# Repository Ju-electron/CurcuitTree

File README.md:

# CurcuitTree
X-MAS Tree what only contain basic IC

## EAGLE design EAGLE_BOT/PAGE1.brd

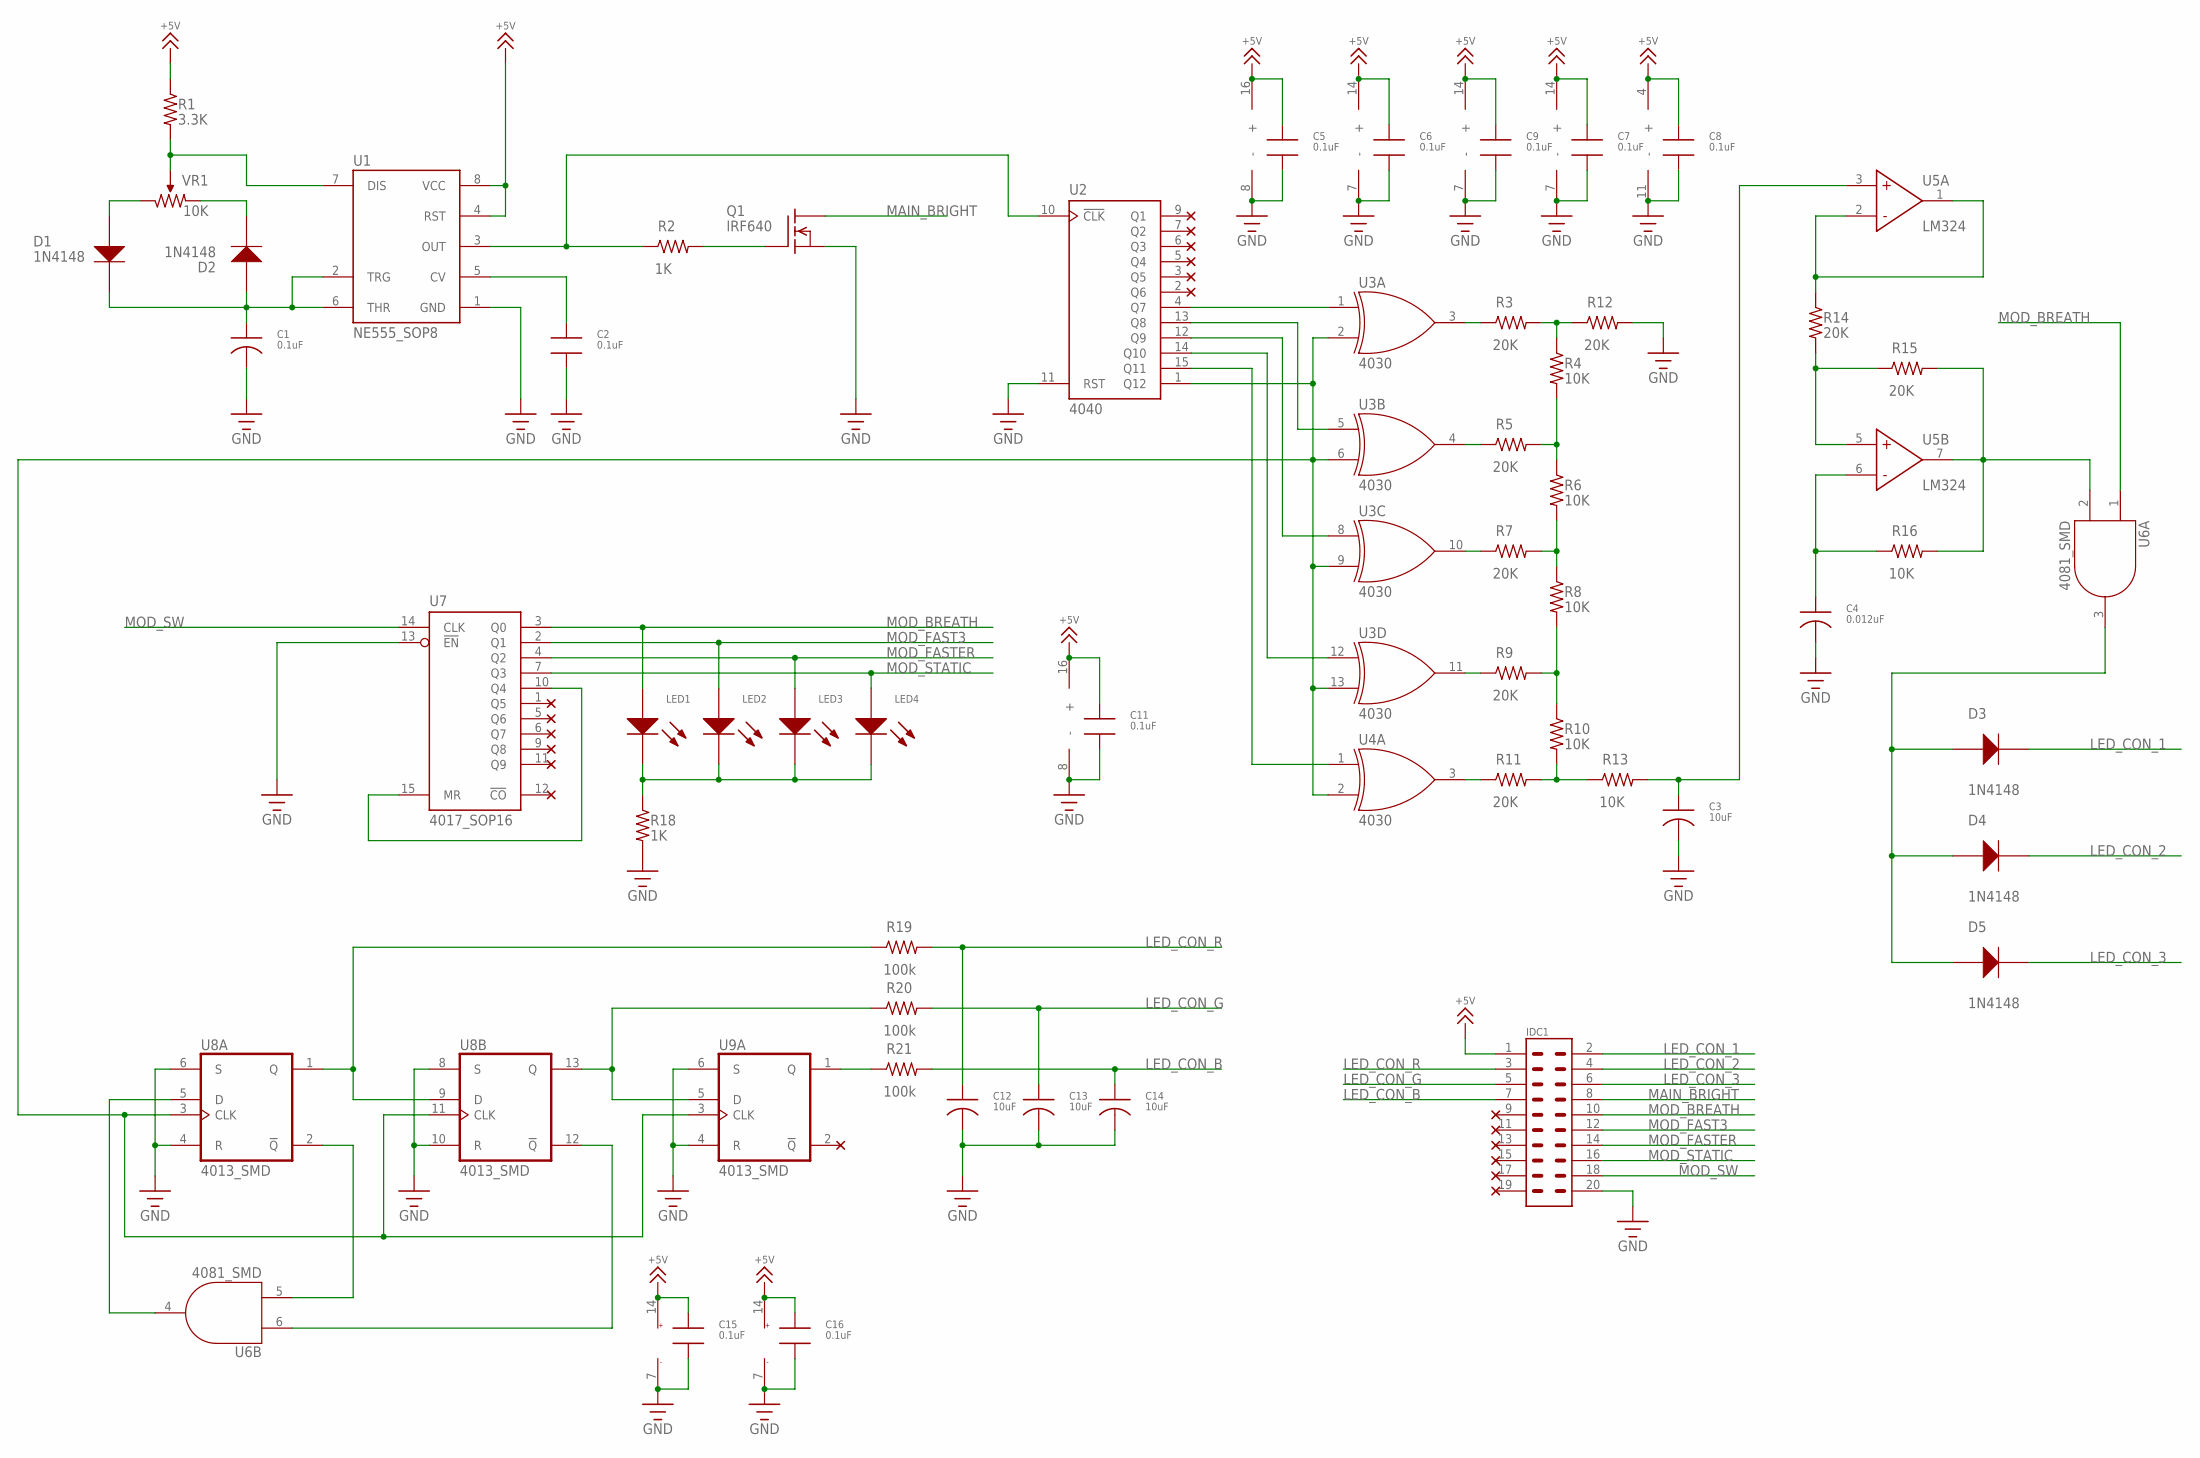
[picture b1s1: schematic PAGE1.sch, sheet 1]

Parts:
C1: 0.1uF; CAP_POL
C2, C5, C6, C7, C8, C9, C11, C15, C16: 0.1uF; SMD2012
C3, C12, C13, C14: 10uF; CAP_POL
C4: 0.012uF; CAP_POL
D1, D2, D3, D4, D5: 1N4148; SMD_DIODE
IDC1: IDC20_BEN; IDC20_BENDING
LED1, LED2, LED3, LED4: LED_BEN; LED_5MM_BEN
Q1: IRF640; TO220
R1: 3.3K; SMD2012
R2, R18: 1K; SMD2012
R3, R5, R7, R9, R11, R12, R14, R15: 20K; SMD2012
R4, R6, R8, R10, R13, R16: 10K; SMD2012
R19, R20, R21: 100k; SMD2012
U1: NE555_SOP8; SOP8
U2: 4040; DIP16
U3, U4: 4030; DIP14
U5: LM324; DIP14
U6: 4081_SMD; SOP14
U7: 4017_SOP16; SOP16
U8, U9: 4013_SMD; SOIC_14
VR1: 10K; 3RP/1610N

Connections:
+5V: C5.1, C6.1, C7.1, C8.1, C9.1, C11.1, C15.1, C16.1, IDC1.1, R1.1, U1.4 (RST), U1.8 (VCC), U2.16 (+), U3.14 (+), U4.14 (+), U5.4 (+), U6.14 (+), U7.16 (+), U8.14 (VCC), U9.14 (VCC); also elsewhere on the board
GND: C1.2, C2.2, C3.2, C4.2, C5.2, C6.2, C7.2, C8.2, C9.2, C11.2, C12.2, C13.2, C14.2, C15.2, C16.2, IDC1.20, Q1.3 (S), R12.2, R18.2, U1.1 (GND), U2.8 (-), U2.11 (RST), U3.7 (-), U4.7 (-), U5.11 (-), U6.7 (-), U7.8 (-), U7.13 (!EN), U8.4 (R), U8.6 (S), U8.7 (GND), U8.8 (S), U8.10 (R), U9.4 (R), U9.6 (S), U9.7 (GND); also elsewhere on the board
LED_CON_1: D3.2, IDC1.2; also elsewhere on the board
LED_CON_2: D4.2, IDC1.4; also elsewhere on the board
LED_CON_3: D5.2, IDC1.6; also elsewhere on the board
LED_CON_B: C14.1, IDC1.7, R21.2
LED_CON_G: C13.1, IDC1.5, R20.2
LED_CON_R: C12.1, IDC1.3, R19.2
MAIN_BRIGHT: IDC1.8, Q1.2 (D)
MOD_BREATH: IDC1.10, LED1.1, U6.1, U7.3 (Q0)
MOD_FAST3: IDC1.12, LED2.1, U7.2 (Q1); also elsewhere on the board
MOD_FASTER: IDC1.14, LED3.1, U7.4 (Q2); also elsewhere on the board
MOD_STATIC: IDC1.16, LED4.1, U7.7 (Q3); also elsewhere on the board
MOD_SW: IDC1.18, U7.14 (CLK)
unnamed: D1.1, VR1.1
unnamed: R1.2, U1.7 (DIS), VR1.2
unnamed: D2.2, VR1.3
unnamed: C2.1, U1.5 (CV)
unnamed: C1.1, D1.2, D2.1, U1.2 (TRG), U1.6 (THR)
unnamed: R2.1, U1.3 (OUT), U2.10 (!CLK)
unnamed: Q1.1 (G), R2.2
unnamed: U2.4 (Q7), U3.1 (IN1)
unnamed: U2.13 (Q8), U3.5 (IN1)
unnamed: U2.12 (Q9), U3.8 (IN1)
unnamed: U2.14 (Q10), U3.12 (IN1)
unnamed: U2.15 (Q11), U4.1 (IN1)
unnamed: R3.1, U3.3 (OUT)
unnamed: R5.1, U3.4 (OUT)
unnamed: R7.1, U3.10 (OUT)
unnamed: R9.1, U3.11 (OUT)
unnamed: R11.1, U4.3 (OUT)
unnamed: R3.2, R4.1, R12.1
unnamed: R4.2, R5.2, R6.1
unnamed: R6.2, R7.2, R8.1
unnamed: R8.2, R9.2, R10.1
unnamed: R10.2, R11.2, R13.1
unnamed: C3.1, R13.2, U5.3 (+)
unnamed: R14.1, U5.1 (OUT), U5.2 (-)
unnamed: R15.2, R16.2, U5.7 (OUT), U6.2
unnamed: R14.2, R15.1, U5.5 (+)
unnamed: C4.1, R16.1, U5.6 (-)
unnamed: D3.1, D4.1, D5.1, U6.3
unnamed: U7.10 (Q4), U7.15 (MR)
unnamed: LED1.2, LED2.2, LED3.2, LED4.2, R18.1
unnamed: U6.5, U8.2 (!Q)
unnamed: U6.6, U8.12 (!Q)
unnamed: U6.4, U8.5 (D)
unnamed: R19.1, U8.1 (Q), U8.9 (D)
unnamed: R20.1, U8.13 (Q), U9.5 (D)
unnamed: U2.1 (Q12), U3.2 (IN2), U3.6 (IN2), U3.9 (IN2), U3.13 (IN2), U4.2 (IN2), U8.3 (CLK), U8.11 (CLK), U9.3 (CLK)
unnamed: R21.1, U9.1 (Q)

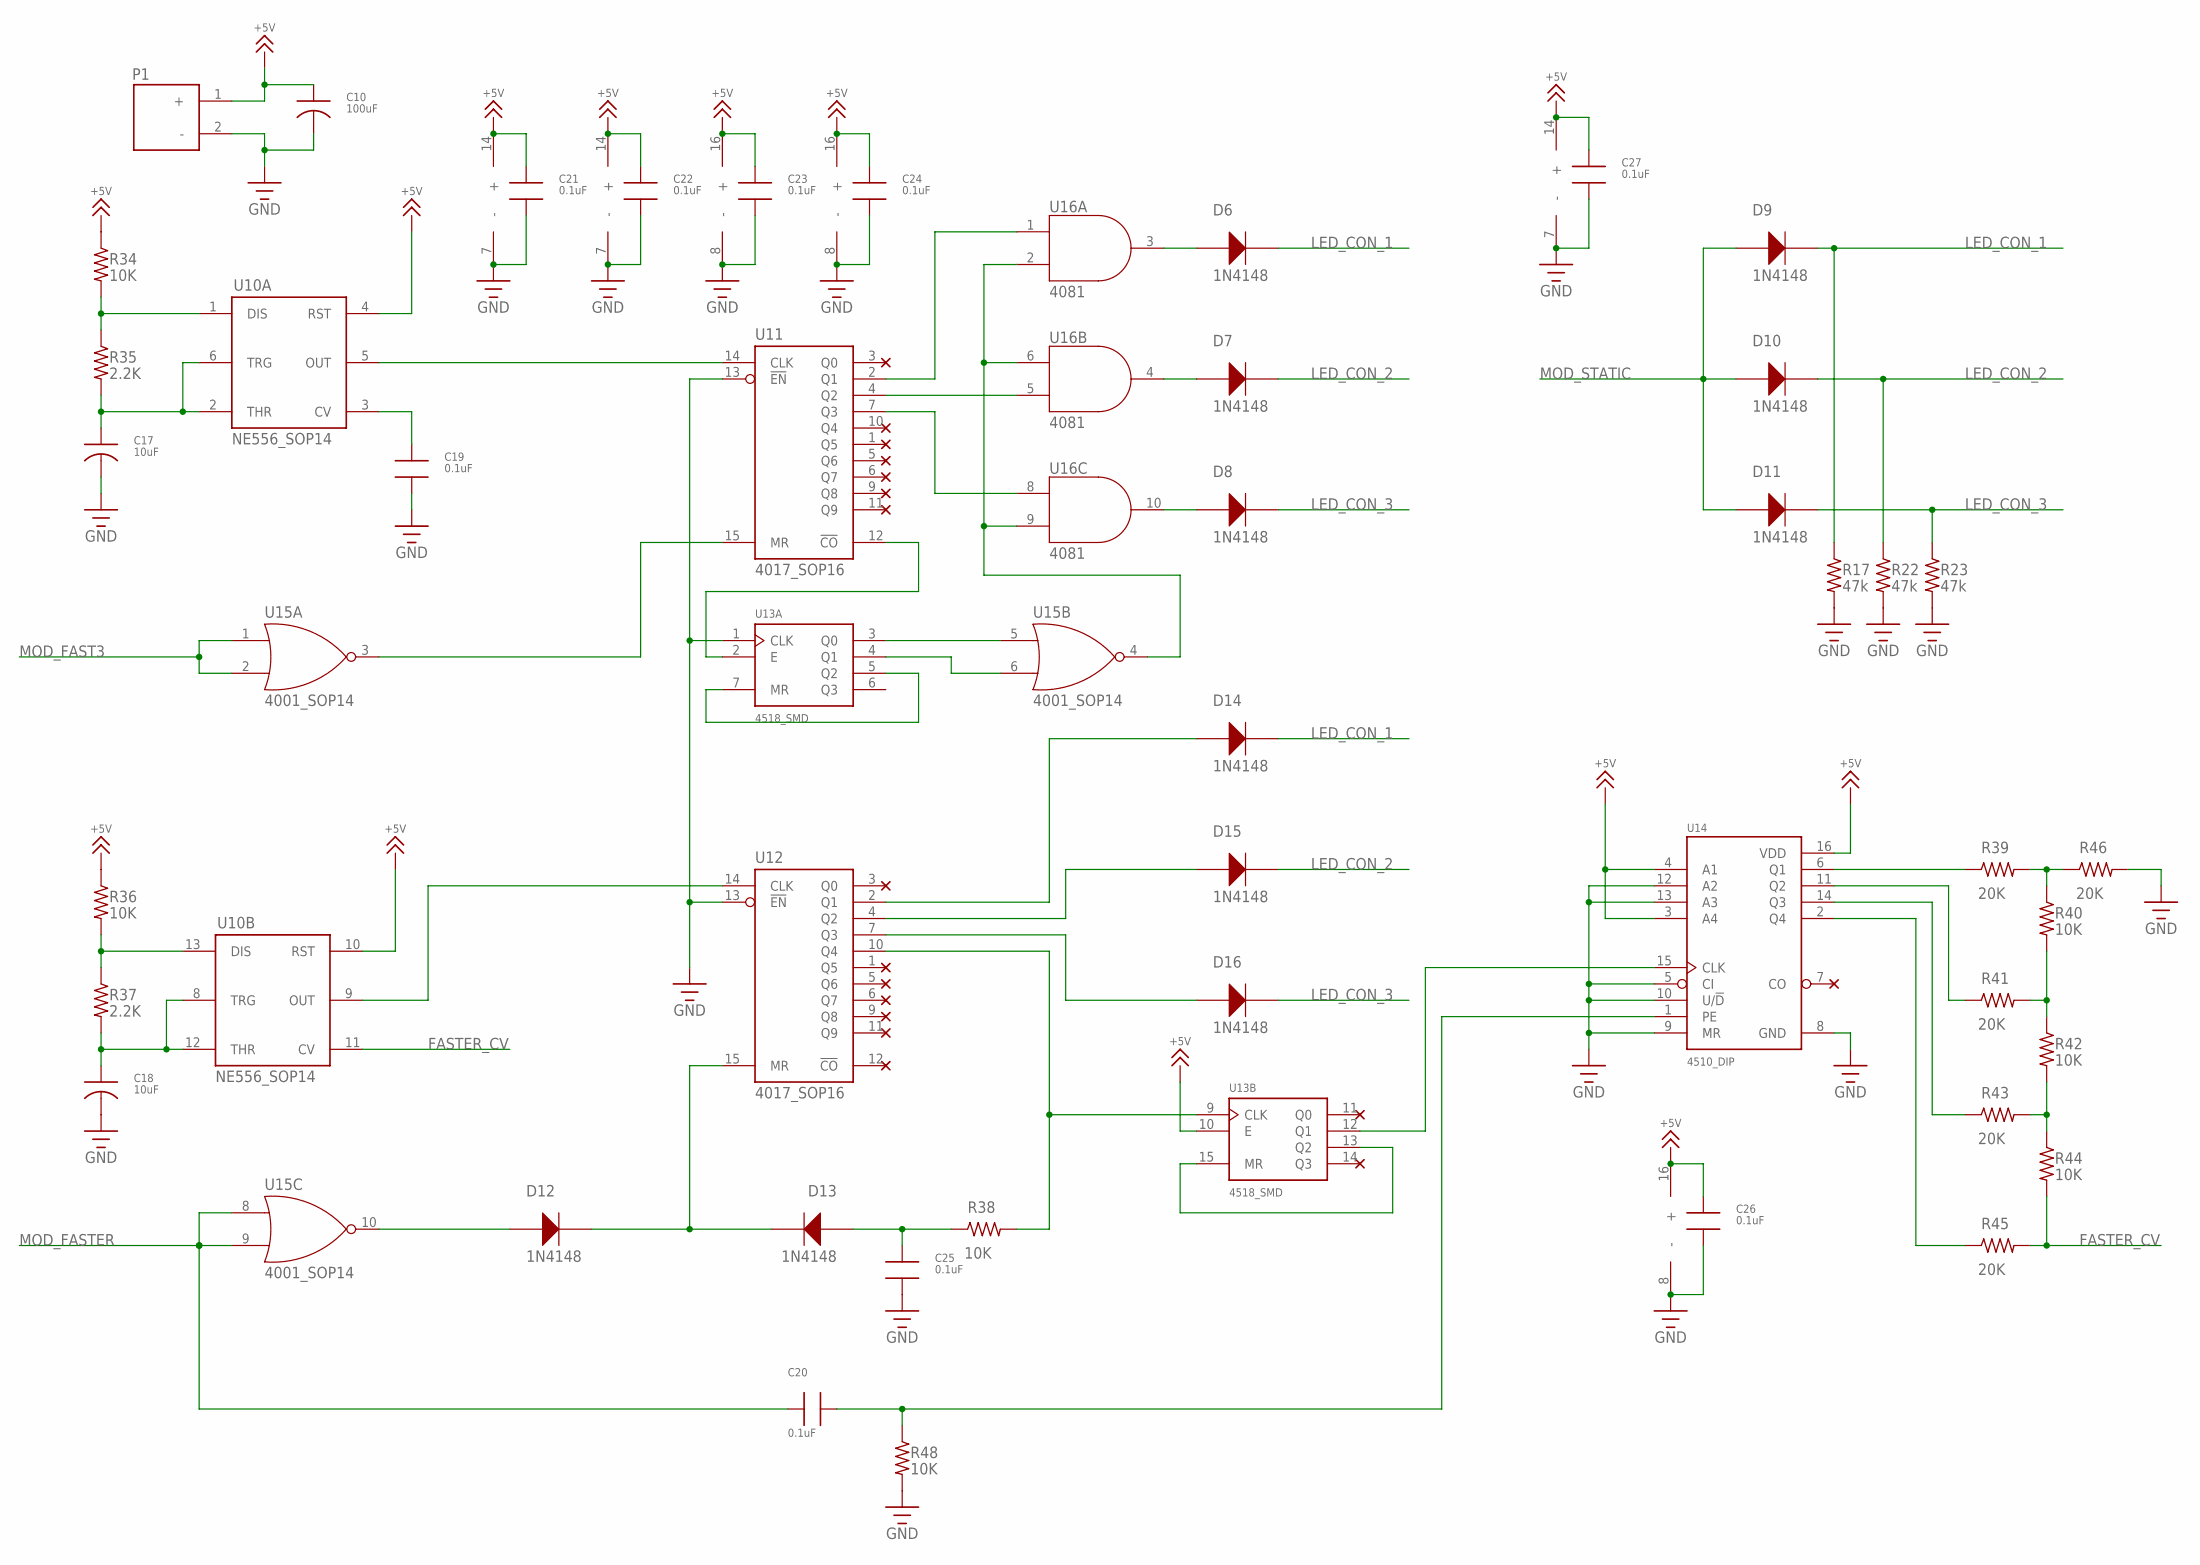
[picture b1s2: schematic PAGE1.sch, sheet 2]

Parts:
C10: 100uF; CAP_POL_BIG
C17, C18: 10uF; CAP_POL
C19, C20, C21, C22, C23, C24, C25, C26, C27: 0.1uF; SMD2012
D6, D7, D8, D9, D10, D11, D12, D13, D14, D15, D16: 1N4148; SMD_DIODE
P1: POWER_2
R17, R22, R23: 47k; SMD2012
R34, R36, R38, R40, R42, R44, R48: 10K; SMD2012
R35, R37: 2.2K; SMD2012
R39, R41, R43, R45, R46: 20K; SMD2012
U10: NE556_SOP14; SOP14
U11, U12: 4017_SOP16; SOP16
U13: 4518_SMD; SOP16
U14: 4510_DIP; DIP16
U15: 4001_SOP14; SOP14
U16: 4081; DIP14

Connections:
+5V: C10.1, C21.1, C22.1, C23.1, C24.1, C26.1, C27.1, P1.1 (+), R34.1, R36.1, U10.4 (RST), U10.10 (RST), U10.14 (+), U11.16 (+), U12.16 (+), U13.10 (E), U13.16 (+), U14.3 (A4), U14.4 (A1), U14.16 (VDD), U15.14 (+), U16.14 (+); also elsewhere on the board
FASTER_CV: R44.2, R45.2, U10.11 (CV)
GND: C10.2, C17.2, C18.2, C19.2, C21.2, C22.2, C23.2, C24.2, C25.2, C26.2, C27.2, P1.2 (-), R17.2, R22.2, R23.2, R46.2, R48.2, U10.7 (-), U11.8 (-), U11.13 (!EN), U12.8 (-), U12.13 (!EN), U13.1 (CLK), U13.8 (-), U14.5 (CI), U14.8 (GND), U14.9 (MR), U14.10 (U/!D), U14.12 (A2), U14.13 (A3), U15.7 (-), U16.7 (-); also elsewhere on the board
LED_CON_1: D6.2, D9.2, D14.2, R17.1; also elsewhere on the board
LED_CON_2: D7.2, D10.2, D15.2, R22.1; also elsewhere on the board
LED_CON_3: D8.2, D11.2, D16.2, R23.1; also elsewhere on the board
MOD_FAST3: U15.1 (IN1), U15.2 (IN2); also elsewhere on the board
MOD_FASTER: C20.1, U15.8 (IN1), U15.9 (IN2); also elsewhere on the board
MOD_STATIC: D9.1, D10.1, D11.1; also elsewhere on the board
unnamed: C17.1, R35.2, U10.2 (THR), U10.6 (TRG)
unnamed: R34.2, R35.1, U10.1 (DIS)
unnamed: U10.5 (OUT), U11.14 (CLK)
unnamed: C19.1, U10.3 (CV)
unnamed: U13.5 (Q2), U13.7 (MR)
unnamed: U11.12 (!CO), U13.2 (E)
unnamed: U11.15 (MR), U15.3 (OUT)
unnamed: U13.3 (Q0), U15.5 (IN1)
unnamed: U13.4 (Q1), U15.6 (IN2)
unnamed: U11.2 (Q1), U16.1
unnamed: U11.4 (Q2), U16.5
unnamed: U11.7 (Q3), U16.8
unnamed: U15.4 (OUT), U16.2, U16.6, U16.9
unnamed: D6.1, U16.3
unnamed: D7.1, U16.4
unnamed: D8.1, U16.10
unnamed: R36.2, R37.1, U10.13 (DIS)
unnamed: C18.1, R37.2, U10.8 (TRG), U10.12 (THR)
unnamed: C20.2, R48.1, U14.1 (PE)
unnamed: U10.9 (OUT), U12.14 (CLK)
unnamed: D12.2, D13.2, U12.15 (MR)
unnamed: R39.1, U14.6 (Q1)
unnamed: D12.1, U15.10 (OUT)
unnamed: D14.1, U12.2 (Q1)
unnamed: D15.1, U12.4 (Q2)
unnamed: D16.1, U12.7 (Q3)
unnamed: C25.1, D13.1, R38.1
unnamed: U13.13 (Q2), U13.15 (MR)
unnamed: R38.2, U12.10 (Q4), U13.9 (CLK)
unnamed: R41.1, U14.11 (Q2)
unnamed: R43.1, U14.14 (Q3)
unnamed: U13.12 (Q1), U14.15 (CLK)
unnamed: R45.1, U14.2 (Q4)
unnamed: R39.2, R40.1, R46.1
unnamed: R40.2, R41.2, R42.1
unnamed: R42.2, R43.2, R44.1

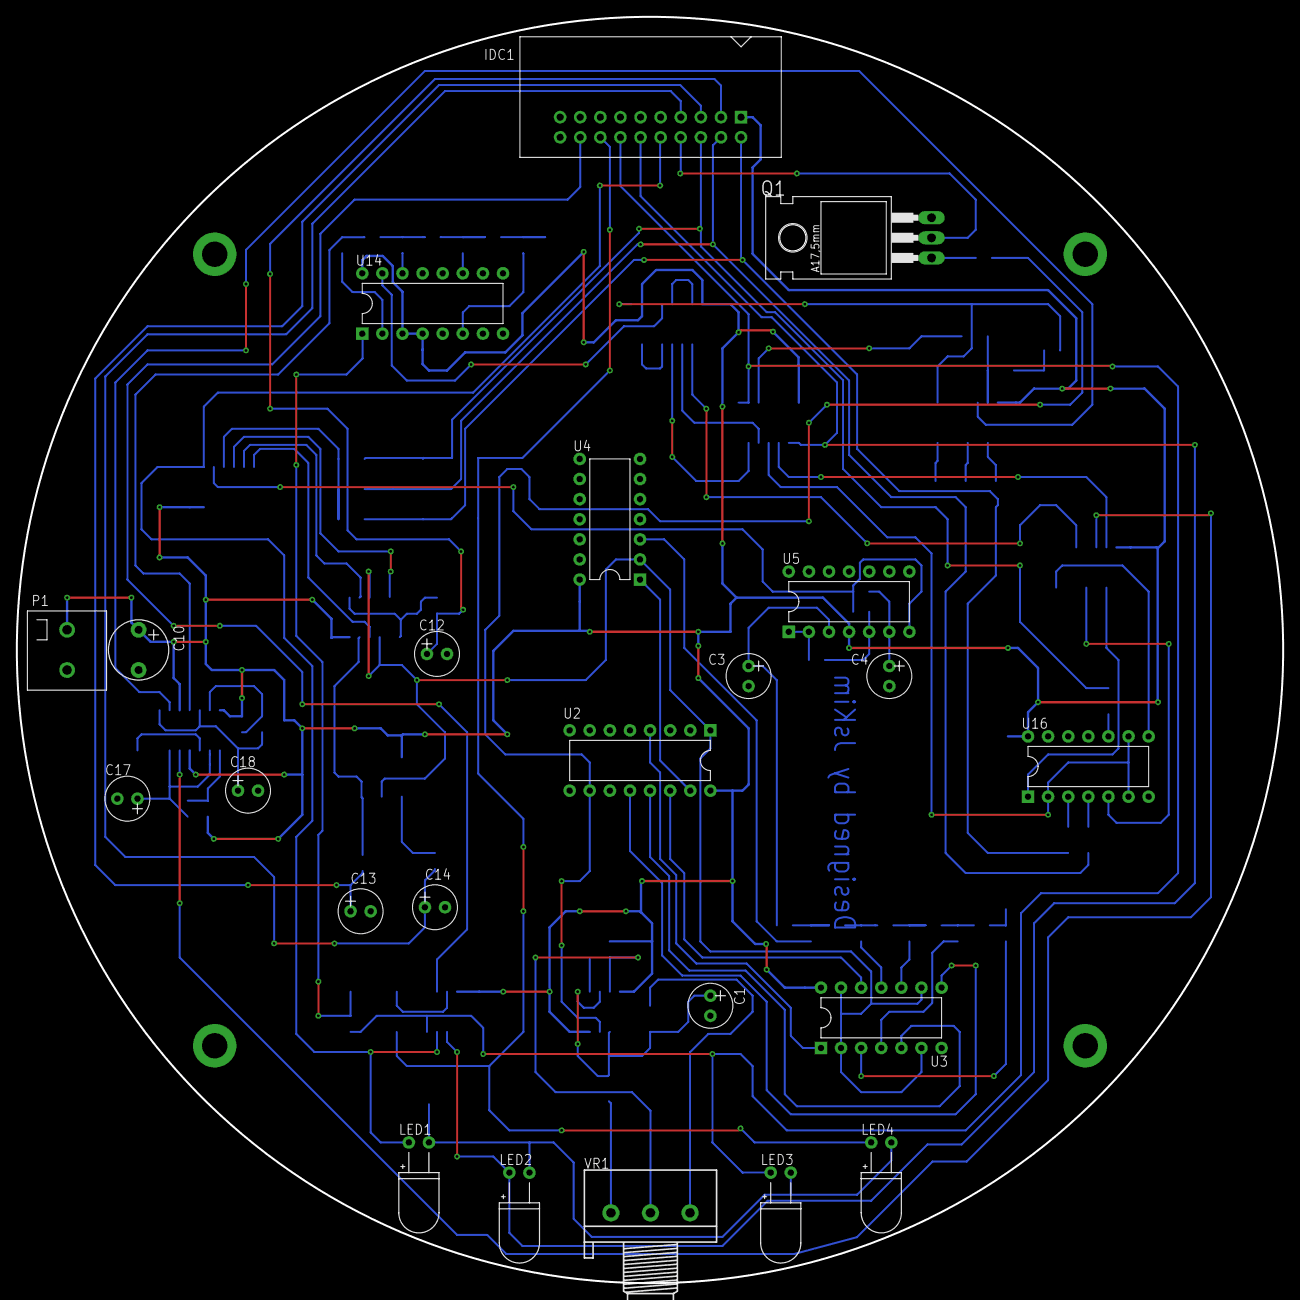
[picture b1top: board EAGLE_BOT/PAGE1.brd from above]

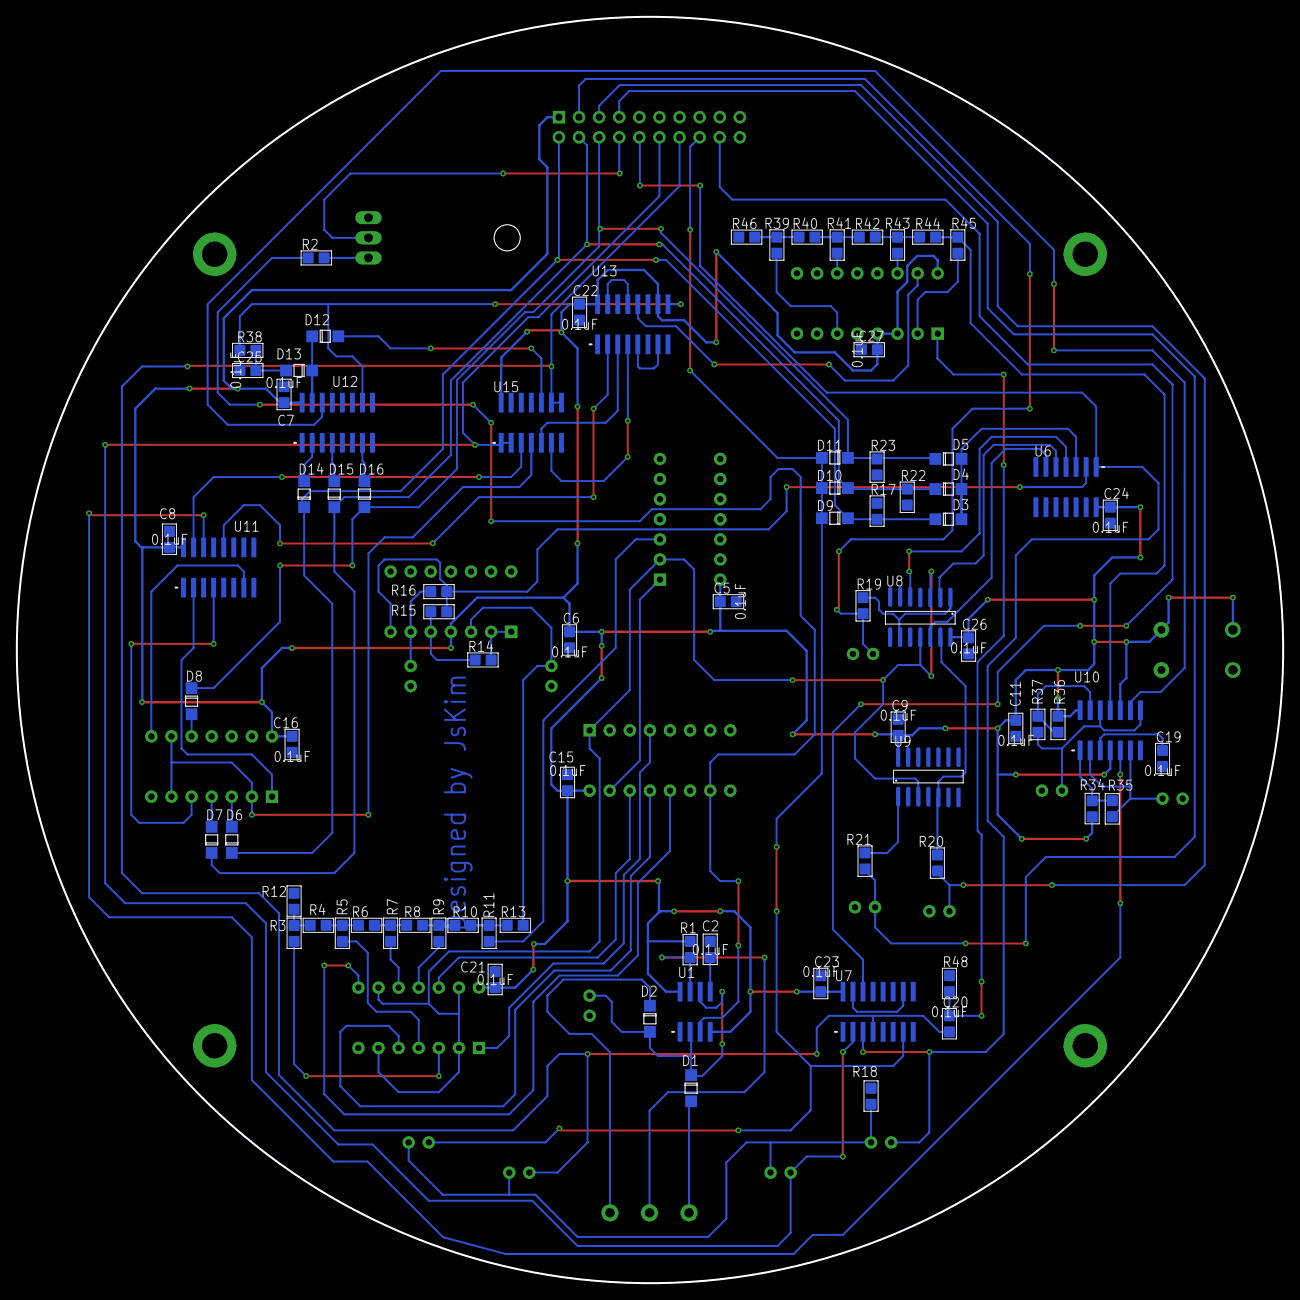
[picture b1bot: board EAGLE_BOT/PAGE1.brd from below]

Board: 2 copper layers, 160.0 x 160.0 mm, 104 parts (81 on the bottom side), 88 nets.

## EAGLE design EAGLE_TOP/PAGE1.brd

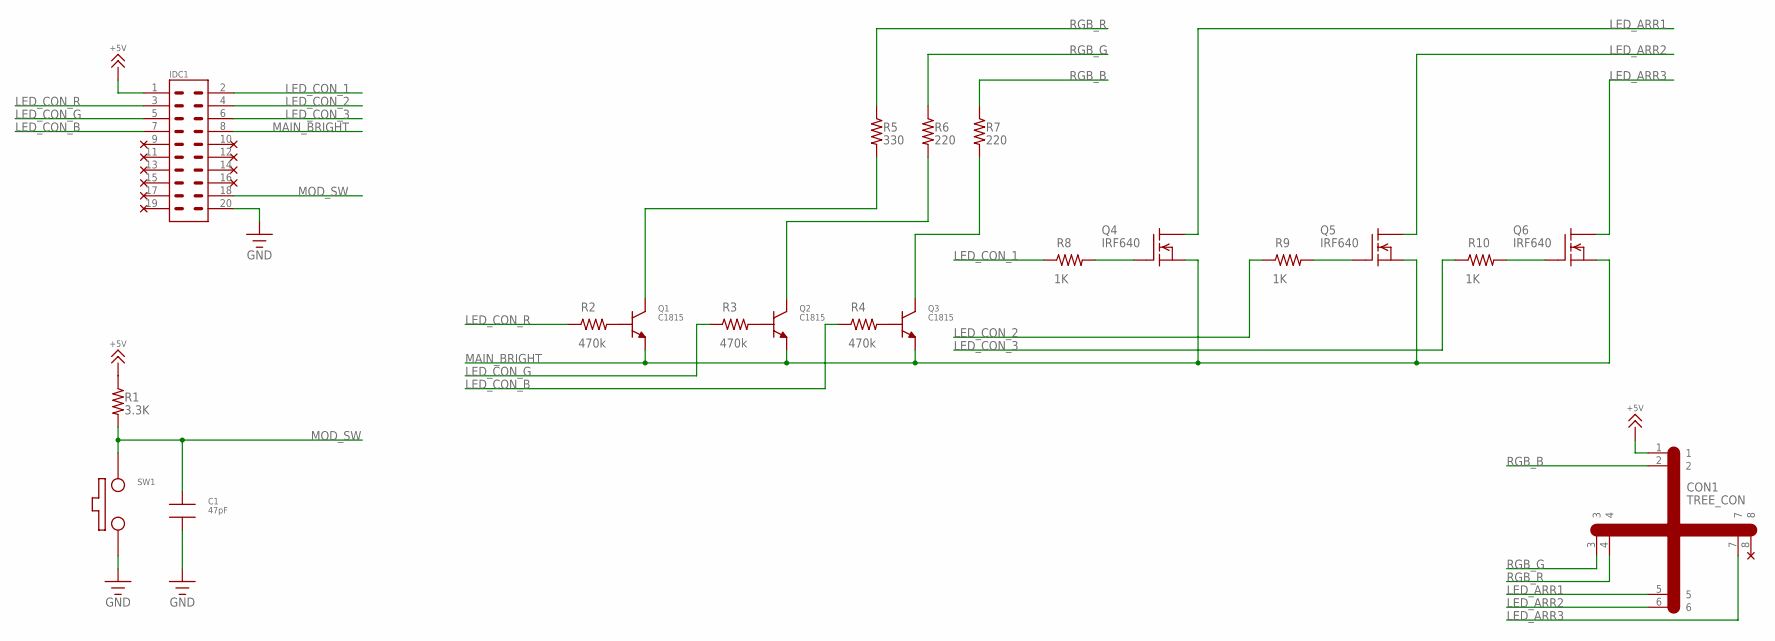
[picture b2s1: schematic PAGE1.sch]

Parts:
C1: 47pF; SMD2012
CON1: TREE_CON
IDC1: IDC20_BEN; IDC20_BENDING
Q1, Q2, Q3: C1815; TO92
Q4, Q5, Q6: IRF640; TO220
R1: 3.3K; SMD2012
R2, R3, R4: 470k; SMD2012
R5: 330; SMD2012
R6, R7: 220; SMD2012
R8, R9, R10: 1K; SMD2012
SW1: PUSH_SW

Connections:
+5V: CON1.1, IDC1.1, R1.1
GND: C1.2, IDC1.20, SW1.P$1
LED_ARR1: CON1.5, Q4.2 (D)
LED_ARR2: CON1.6, Q5.2 (D)
LED_ARR3: CON1.7, Q6.2 (D)
LED_CON_1: IDC1.2, R8.1
LED_CON_2: IDC1.4, R9.1
LED_CON_3: IDC1.6, R10.1
LED_CON_B: IDC1.7, R4.1
LED_CON_G: IDC1.5, R3.1
LED_CON_R: IDC1.3, R2.1
MAIN_BRIGHT: IDC1.8, Q1.1 (E), Q2.1 (E), Q3.1 (E), Q4.3 (S), Q5.3 (S), Q6.3 (S)
MOD_SW: C1.1, IDC1.18, R1.2, SW1.P$2
unnamed: Q4.1 (G), R8.2
unnamed: Q5.1 (G), R9.2
unnamed: Q6.1 (G), R10.2
unnamed: Q1.3 (B), R2.2
unnamed: Q2.3 (B), R3.2
unnamed: Q3.3 (B), R4.2
unnamed: Q1.2 (C), R5.2
unnamed: Q2.2 (C), R6.2
unnamed: Q3.2 (C), R7.2
RGB_B: CON1.2, R7.1
RGB_G: CON1.3, R6.1
RGB_R: CON1.4, R5.1

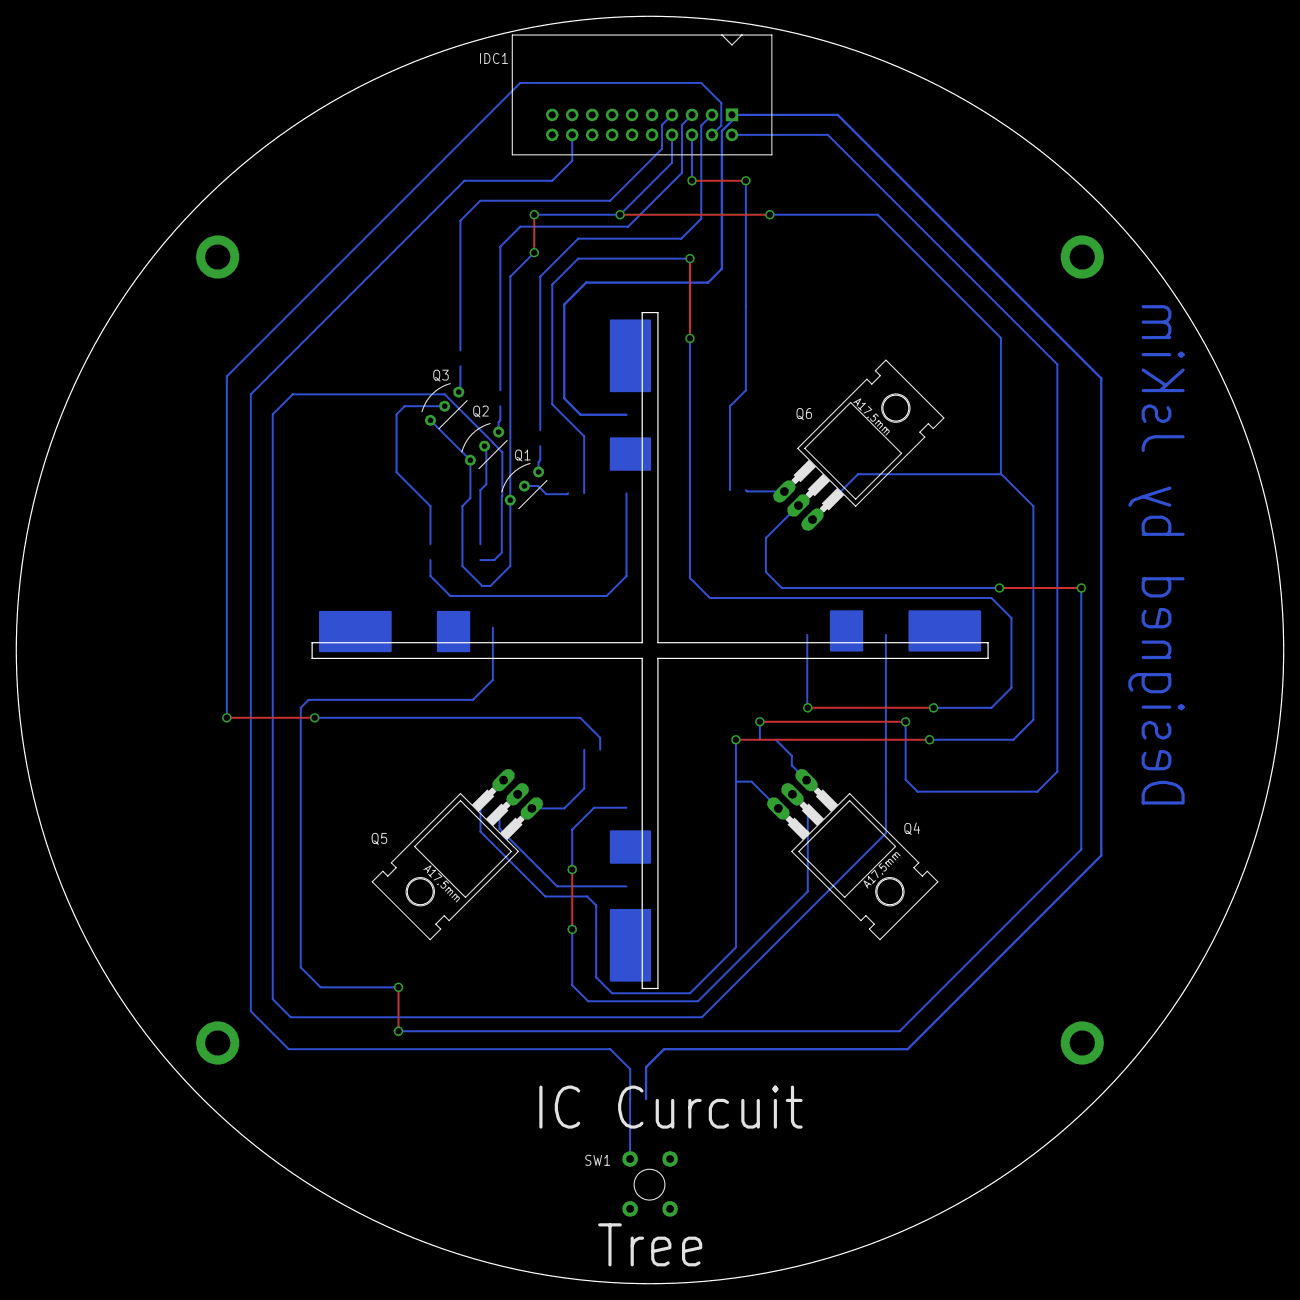
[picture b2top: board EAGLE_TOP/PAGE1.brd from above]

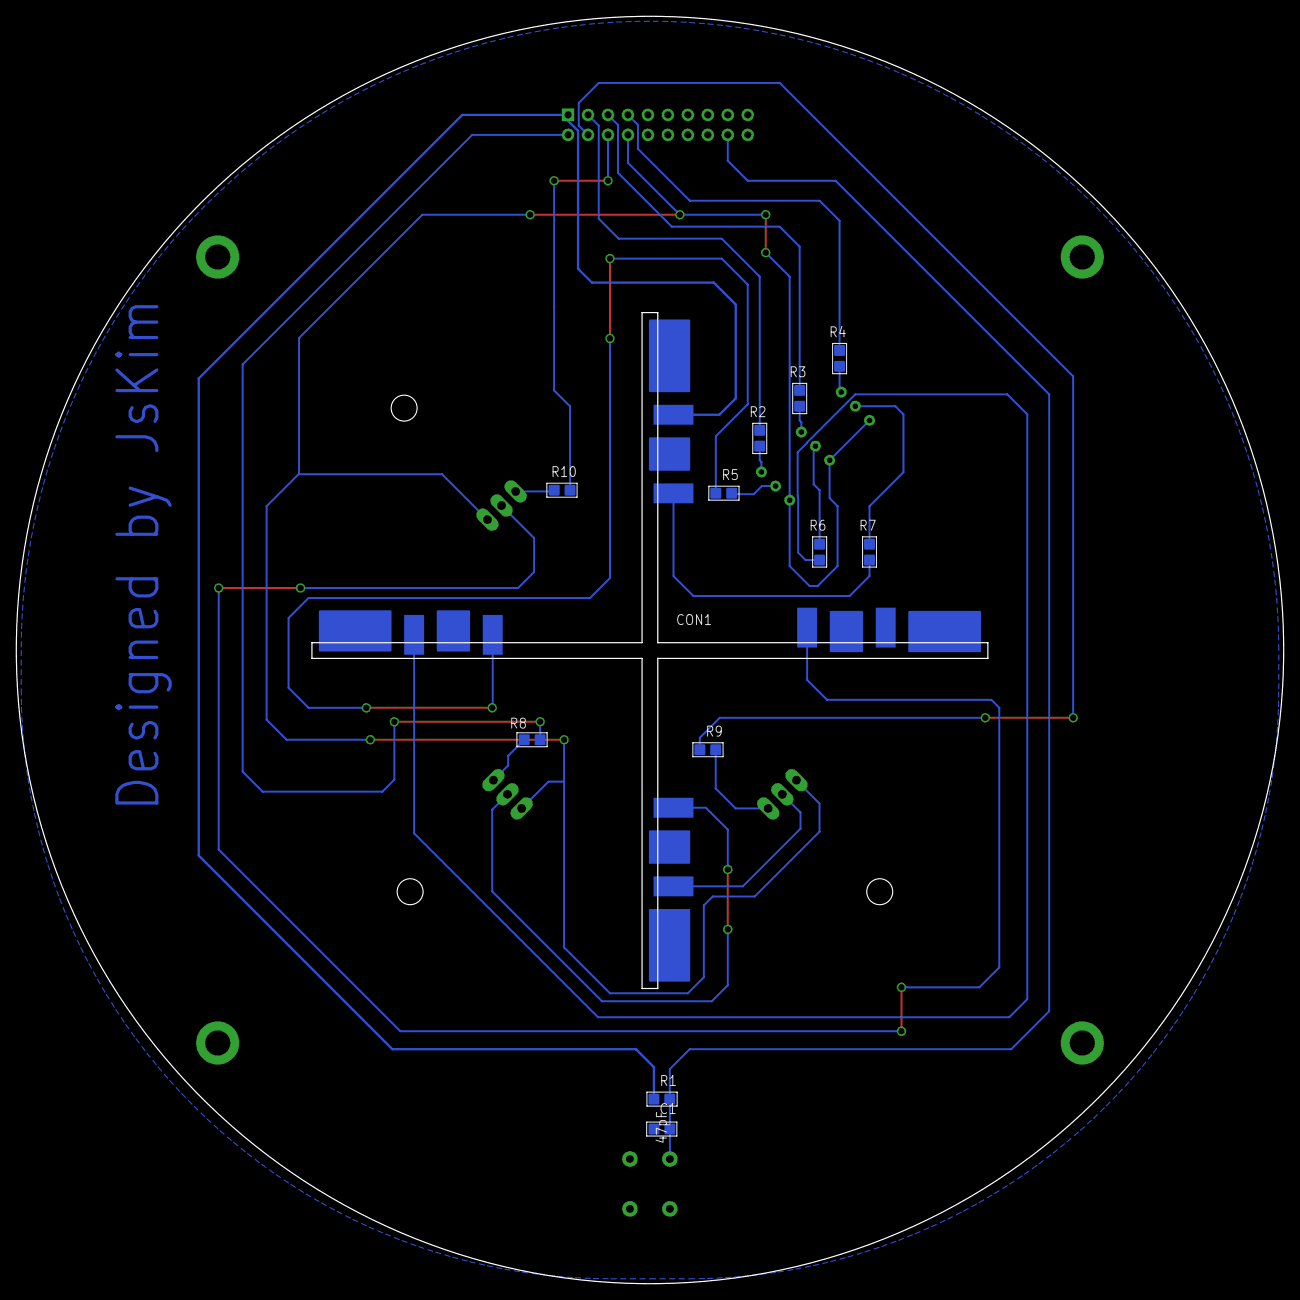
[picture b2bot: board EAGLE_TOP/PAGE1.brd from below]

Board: 2 copper layers, 161.2 x 161.2 mm, 20 parts (12 on the bottom side), 25 nets.

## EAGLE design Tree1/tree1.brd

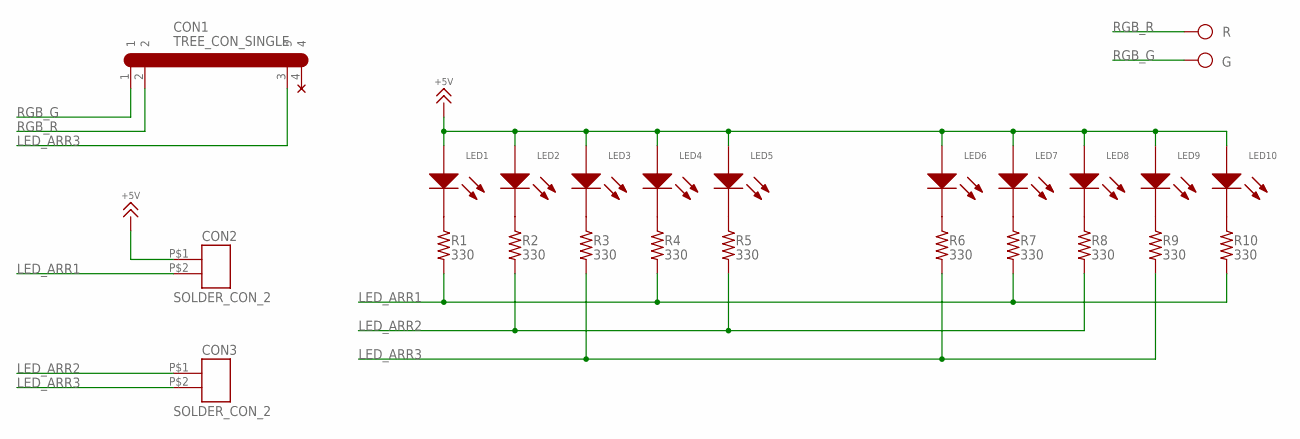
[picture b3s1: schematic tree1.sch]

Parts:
CON1: TREE_CON_SINGLE
CON2, CON3: SOLDER_CON_2
G: TP
LED1, LED2, LED3, LED4, LED5, LED6, LED7, LED8, LED9, LED10: LED_BEN; LED_5MM_BEN
R: TP
R1, R2, R3, R4, R5, R6, R7, R8, R9, R10: 330; SMD2012

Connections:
+5V: CON2.P$1, LED1.1, LED2.1, LED3.1, LED4.1, LED5.1, LED6.1, LED7.1, LED8.1, LED9.1, LED10.1
LED_ARR1: CON2.P$2, R1.2, R4.2, R7.2, R10.2
LED_ARR2: CON3.P$1, R2.2, R5.2, R8.2
LED_ARR3: CON1.3, CON3.P$2, R3.2, R6.2, R9.2
unnamed: LED1.2, R1.1
unnamed: LED2.2, R2.1
unnamed: LED3.2, R3.1
unnamed: LED4.2, R4.1
unnamed: LED5.2, R5.1
unnamed: LED6.2, R6.1
unnamed: LED7.2, R7.1
unnamed: LED8.2, R8.1
unnamed: LED9.2, R9.1
unnamed: LED10.2, R10.1
RGB_G: CON1.1, G.1
RGB_R: CON1.2, R.1

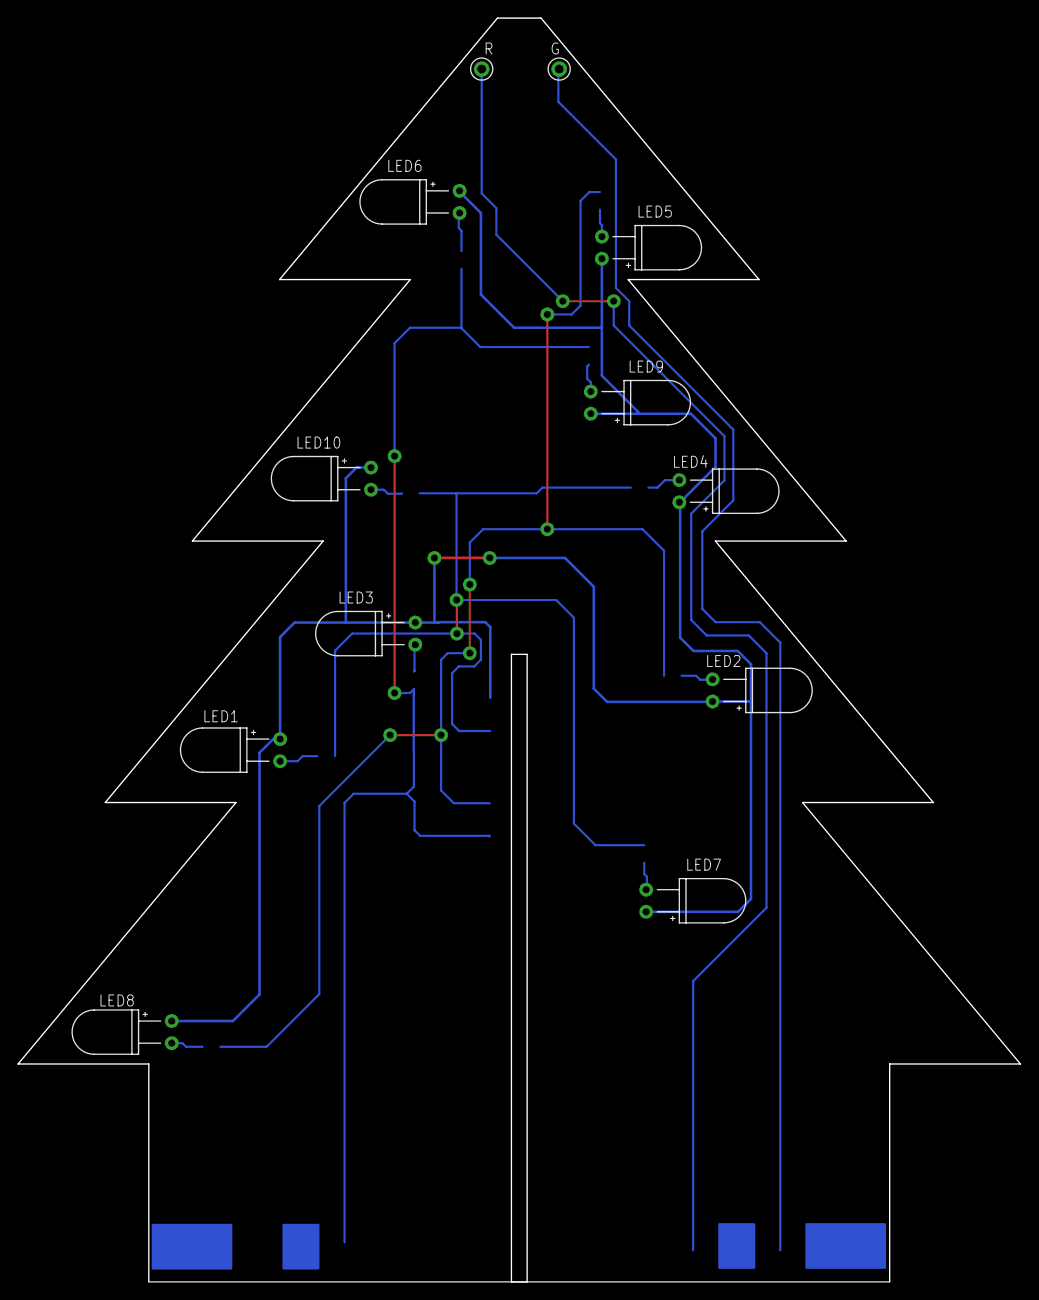
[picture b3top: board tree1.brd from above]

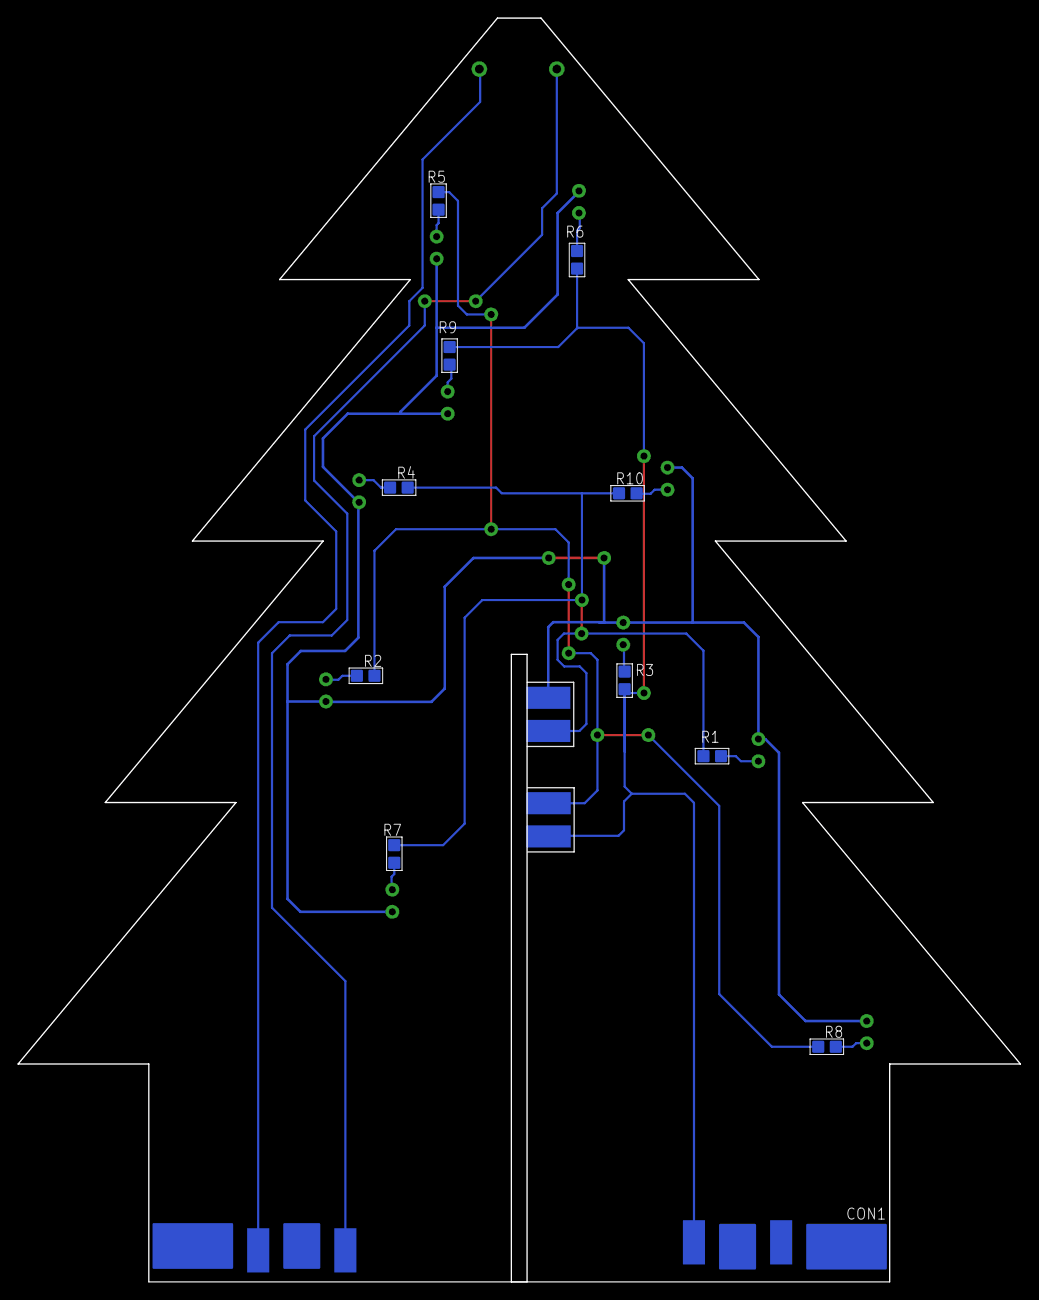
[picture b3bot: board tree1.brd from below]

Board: 2 copper layers, 115.0 x 145.0 mm, 25 parts (13 on the bottom side), 16 nets.

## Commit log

2022-01-03 TEST PCB Complete
2022-01-03 test commit
2022-01-03 add txt
2022-01-03 hello
2022-01-04 ALL Deleted
2022-01-04 first upload
2022-01-10 bottom PCB completed
2022-01-10 add bot schematic
2022-01-10 top PCB completed
2022-01-10 Tree PCB Cmpl, top PCB Mdfi
2022-01-13 Operation Complete
2022-01-13 ver1 Complete
